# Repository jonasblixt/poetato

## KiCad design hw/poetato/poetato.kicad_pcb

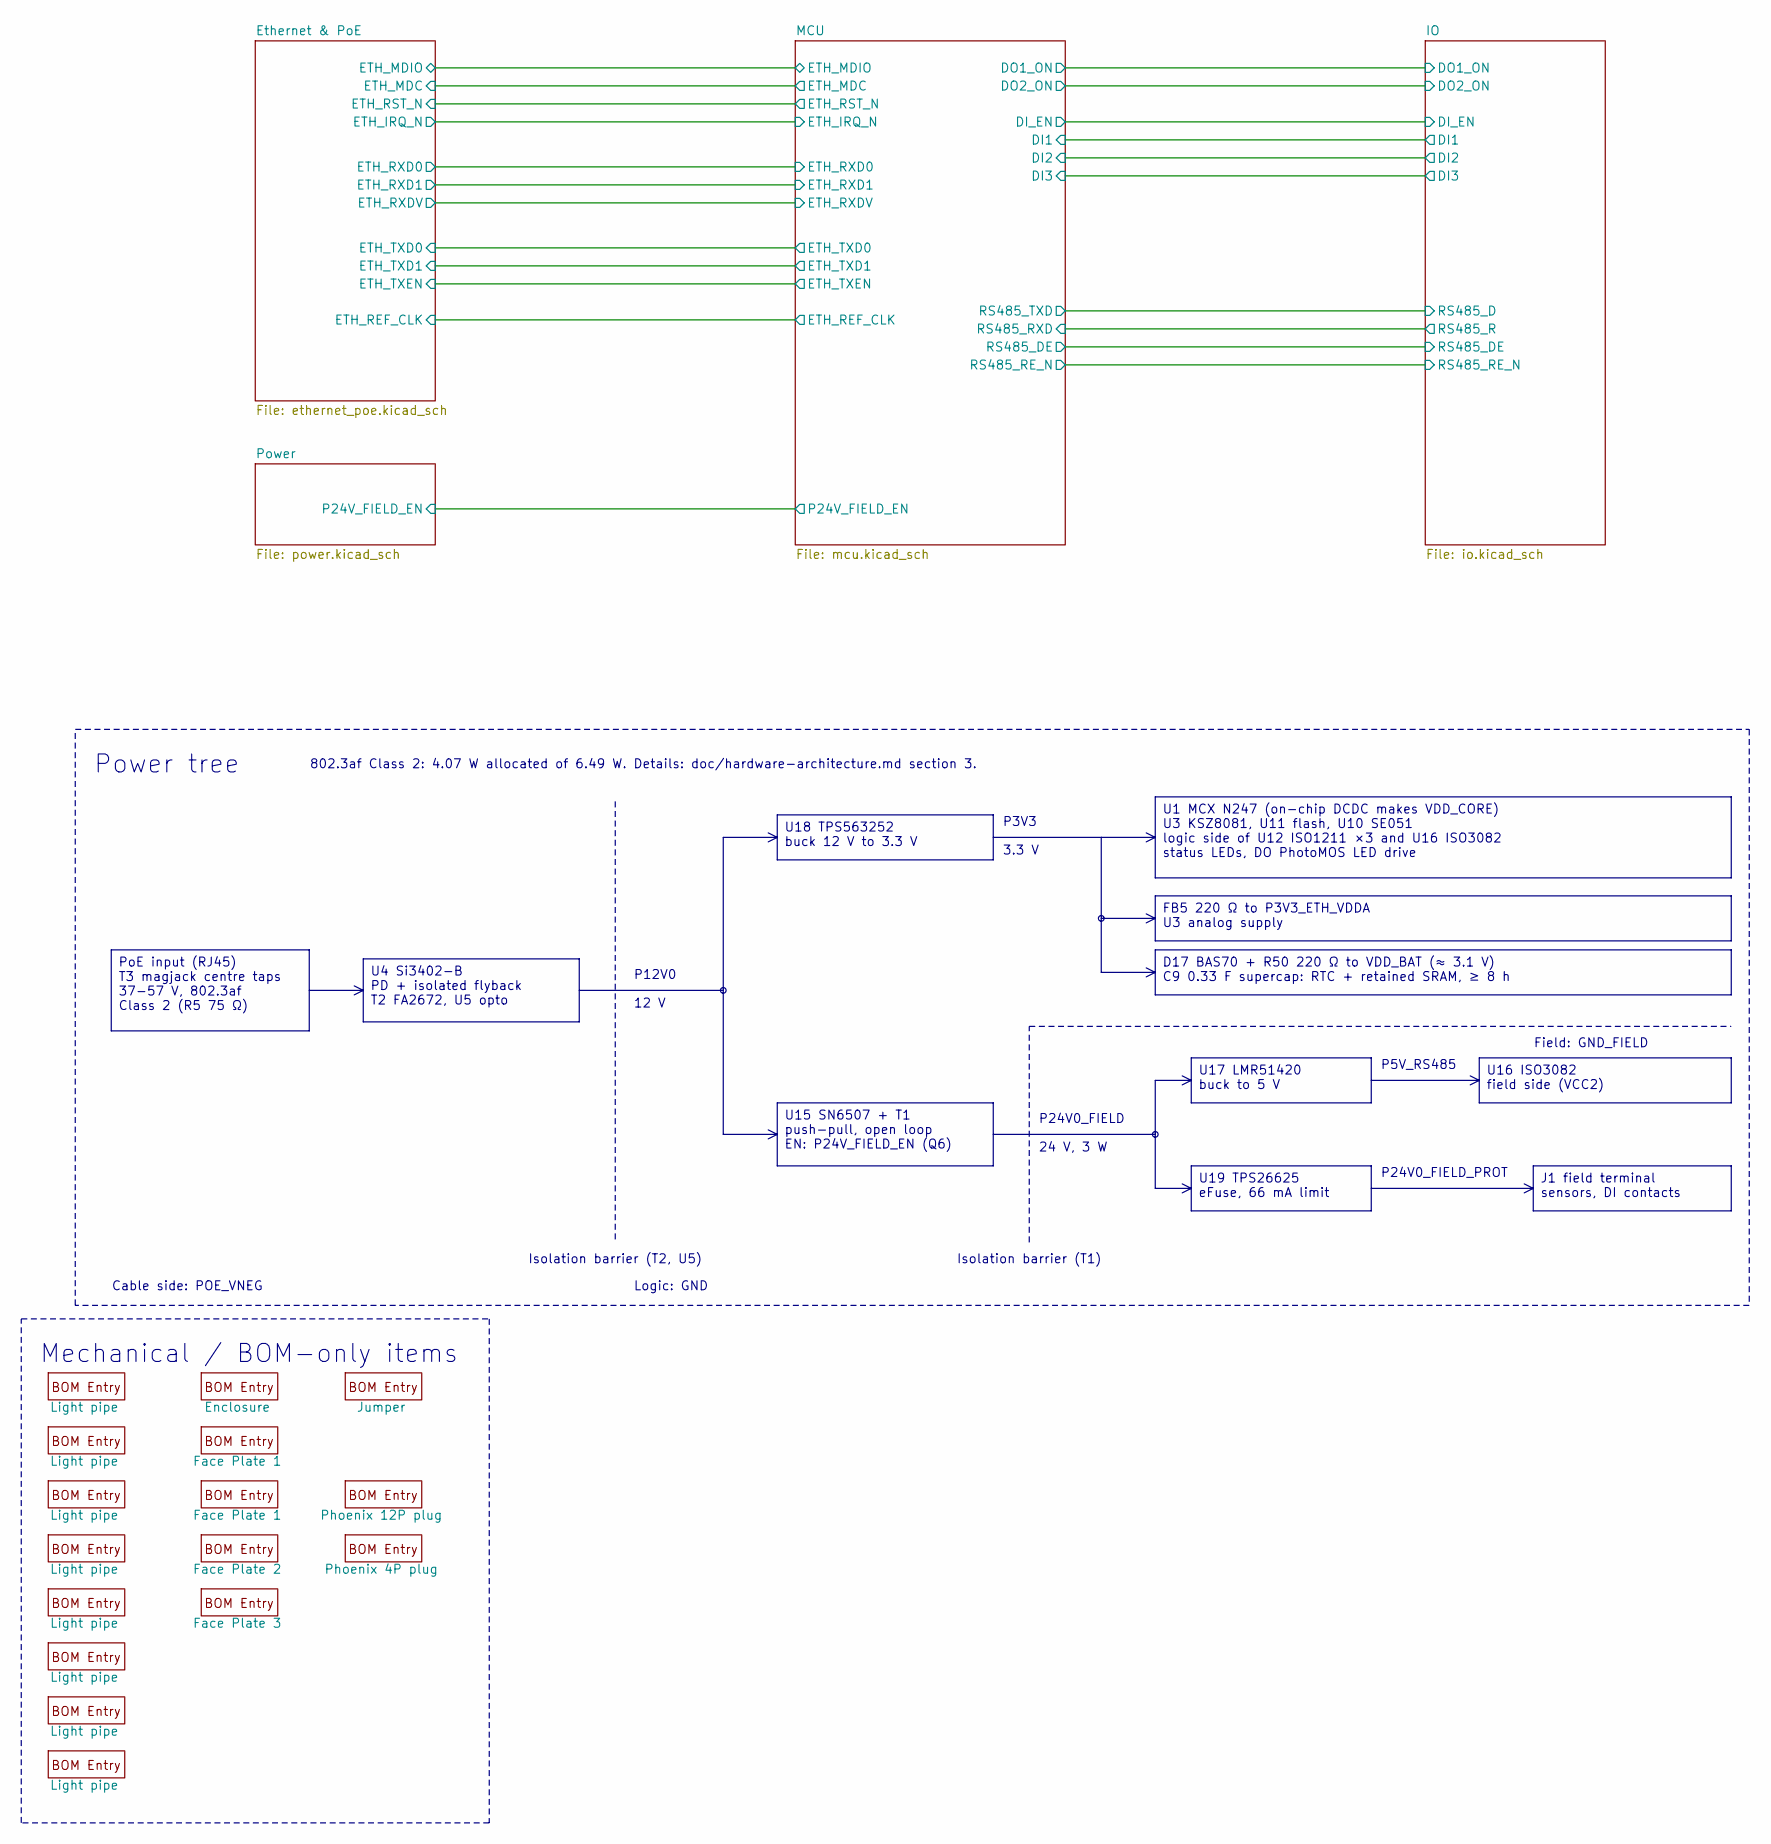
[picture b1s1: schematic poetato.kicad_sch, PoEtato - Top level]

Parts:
M1, M2, M3, M4, M5, M6, M7, M8: Light pipe; Part Number PLP2-750
M9: Enclosure; Part Number 35.0807000.BL
M10: Jumper; Part Number 60900213421
M11, M12: Face Plate 1; Part Number P05040206T.BL
M13: Face Plate 2; Part Number P05040201T.BL
M14: Face Plate 3; Part Number P05040254T.BL
M15: Phoenix 12P plug; Part Number 1757116
M16: Phoenix 4P plug; Part Number 1757035

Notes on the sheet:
P12V0
802.3af Class 2: 4.07 W allocated of 6.49 W. Details: doc/hardware-architecture.md section 3.
P5V_RS485
Power tree
P3V3
P24V0_FIELD_PROT
Field: GND_FIELD
Mechanical / BOM-only items
Logic: GND
Isolation barrier (T1)
Isolation barrier (T2, U5)
24 V, 3 W
Cable side: POE_VNEG
12 V
P24V0_FIELD
3.3 V
U18 TPS563252 buck 12 V to 3.3 V
U15 SN6507 + T1 push-pull, open loop EN: P24V_FIELD_EN (Q6)
U16 ISO3082 field side (VCC2)
PoE input (RJ45) T3 magjack centre taps 37-57 V, 802.3af Class 2 (R5 75 Ω)
FB5 220 Ω to P3V3_ETH_VDDA U3 analog supply
U19 TPS26625 eFuse, 66 mA limit
D17 BAS70 + R50 220 Ω to VDD_BAT (≈ 3.1 V) C9 0.33 F supercap: RTC + retained SRAM, ≥ 8 h
U1 MCX N247 (on-chip DCDC makes VDD_CORE) U3 KSZ8081, U11 flash, U10 SE051 logic side of U12 ISO1211 ×3 and U16 ISO3082 status LEDs, DO PhotoMOS LED drive
U4 Si3402-B PD + isolated flyback T2 FA2672, U5 opto
J1 field terminal sensors, DI contacts
U17 LMR51420 buck to 5 V

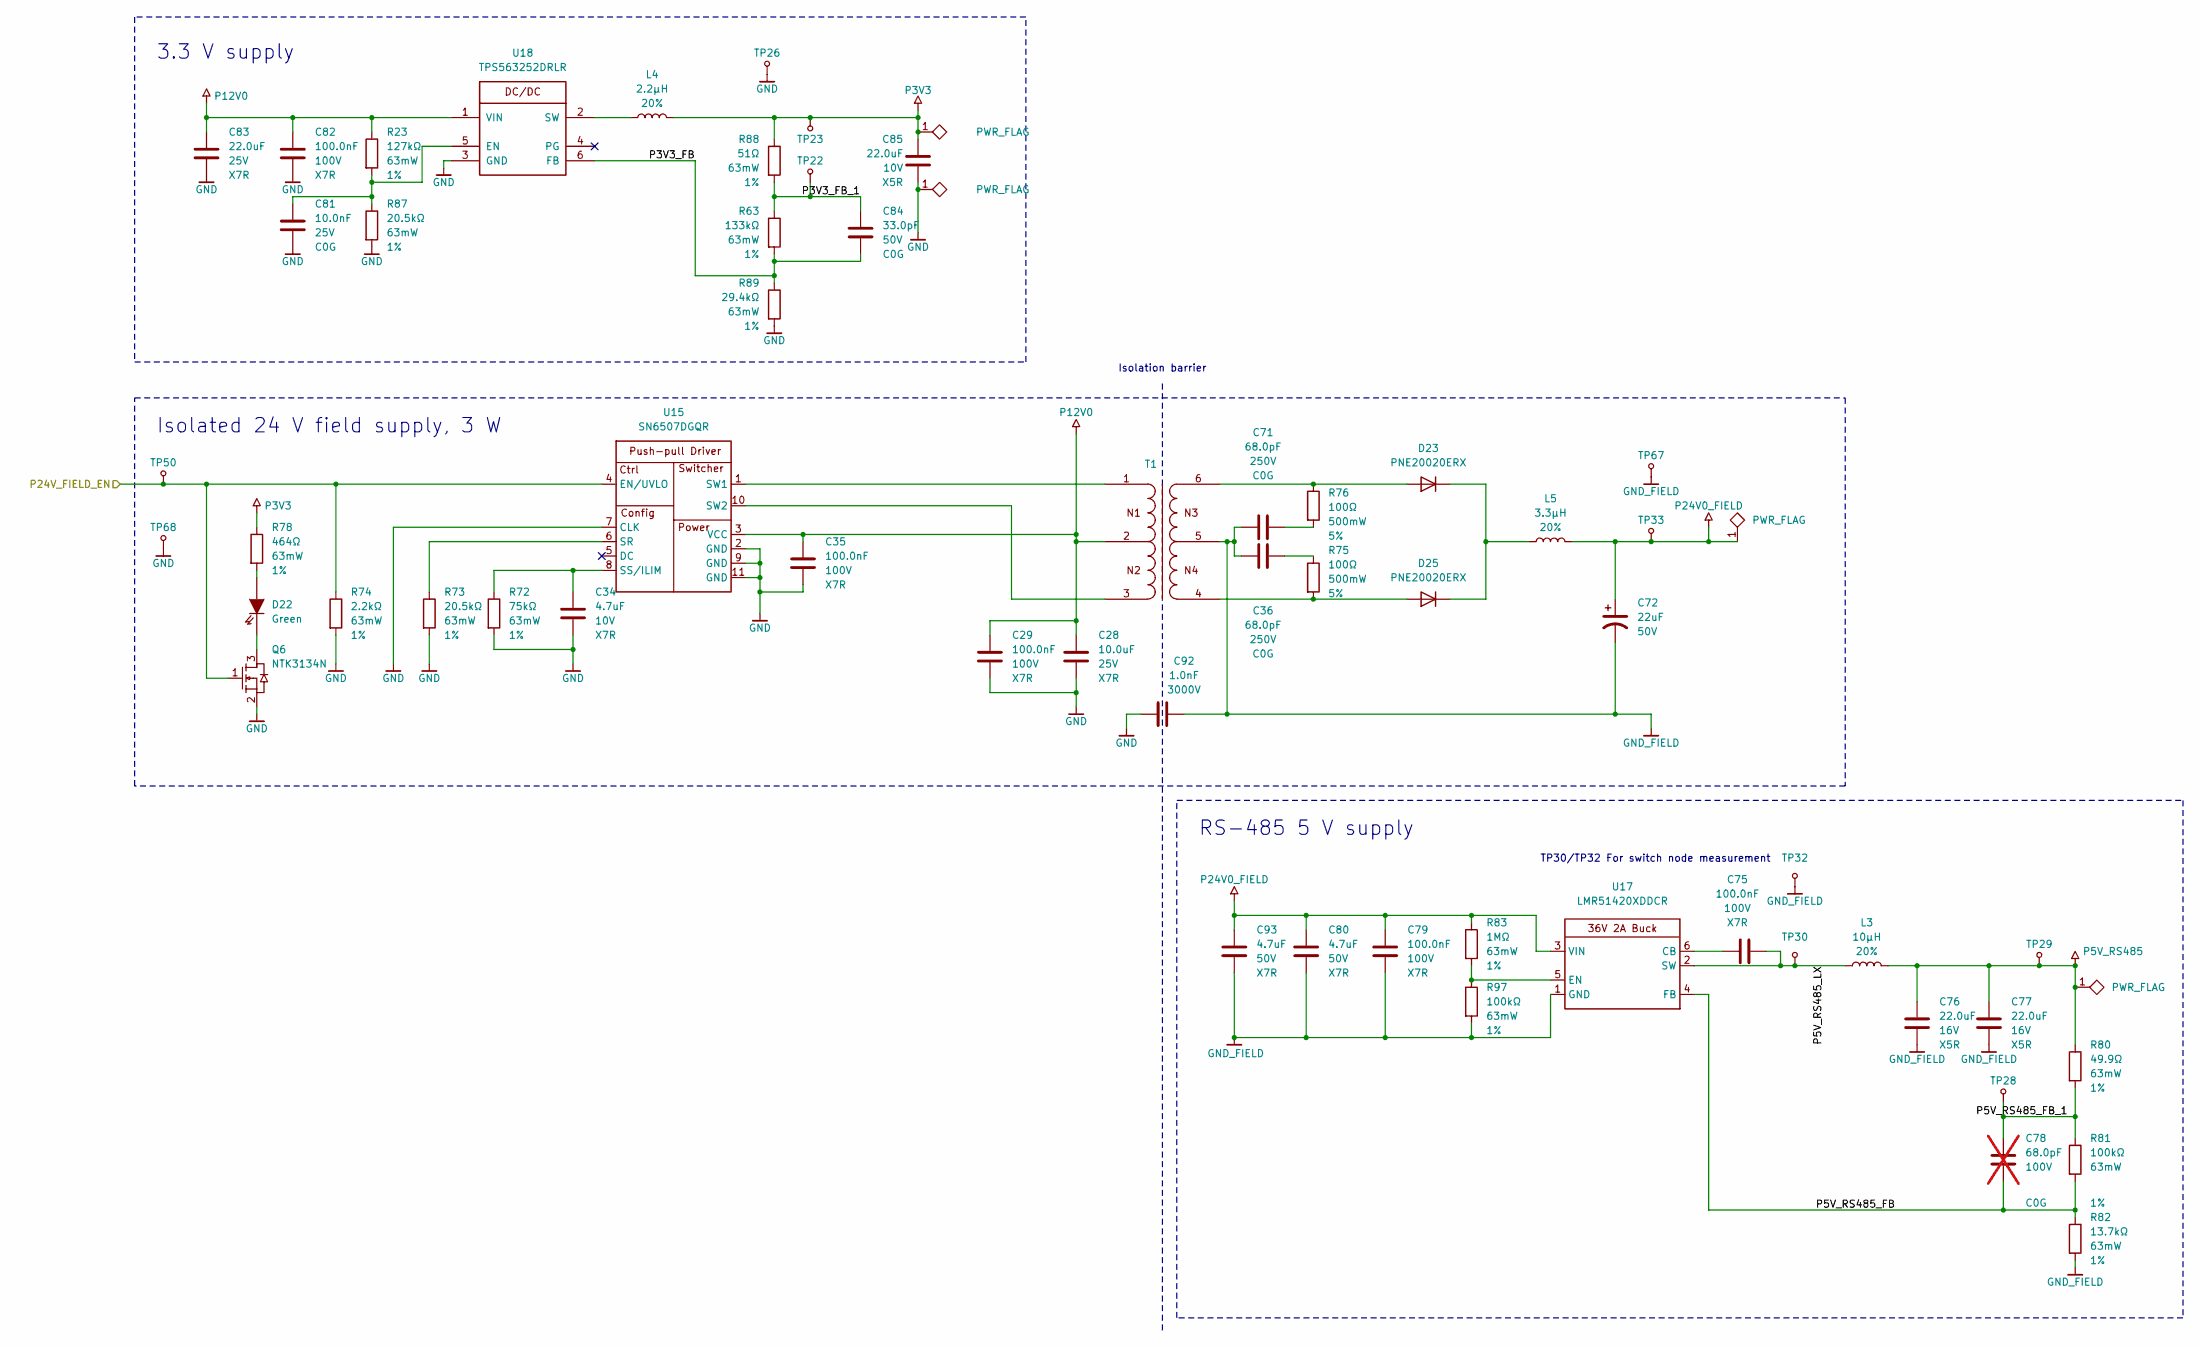
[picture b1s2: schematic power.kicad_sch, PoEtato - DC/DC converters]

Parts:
C28: 10.0uF; C_0805_2012Metric; Voltage 25V; Part Number GRM21BZ71E106KE15
C29, C35, C75, C79, C82: 100.0nF; C_0603_1608Metric; Voltage 100V; Part Number GRM188R72A104KA35
C34: 4.7uF; C_0603_1608Metric; Voltage 10V; Part Number GRM188Z71A475KE15
C36, C71: 68.0pF; C_0603_1608Metric; Voltage 250V; Part Number GQM1875C2E680JB12
C72: 22uF; CP_Elec_5x5.8; Voltage 50V; Part Number EMZR500ARA220ME61G
C76, C77: 22.0uF; C_0805_2012Metric; Voltage 16V; Part Number GRM21BR61C226ME44
C78: 68.0pF; C_0402_1005Metric; Voltage 100V; Part Number GRM1555C2A680JA01; not fitted
C80, C93: 4.7uF; C_1206_3216Metric; Voltage 50V; Part Number GRM31CR71H475KA12
C81: 10.0nF; C_0402_1005Metric; Voltage 25V; Part Number GRM1555C1E103JE01
C83: 22.0uF; C_1210_3225Metric; Voltage 25V; Part Number GRM32ER71E226KE15
C84: 33.0pF; C_0402_1005Metric; Voltage 50V; Part Number GRM1555C1H330GA01
C85: 22.0uF; C_0603_1608Metric; Voltage 10V; Part Number GRM188R61A226ME15
C92: 1.0nF; C_1808_4520Metric; Voltage 3000V; Part Number C1808C102KHRACTU
D22: LED0402_150040VS73240; LED_0402_1005Metric; Part Number 150040VS73240
D23, D25: PNE20020ERX; Nexperia_CFP3_SOD-123W; Part Number PNE20020ERX
L3: 10µH; IHLP2020CZ; Tolerance 20%; Part Number IHLP2020CZER100M01
L4: 2.2µH; IHLP1212BZ; Tolerance 20%; Part Number IHLP1212BZEZ2R2M1Z
L5: 3.3µH; IHLP1212BZ; Tolerance 20%; Part Number IHLP1212BZEZ3R3M1Z
Q6: NTK3134N; SOT-723; Part Number NTK3134NT1G
R23: 127kΩ; R_0402_1005Metric; Tolerance 1%; Part Number CRCW0402127KFKED
R63: 133kΩ; R_0402_1005Metric; Tolerance 1%; Part Number CRCW0402133KFKED
R72: 75kΩ; R_0402_1005Metric; Tolerance 1%; Part Number CRCW040275K0FKED
R73, R87: 20.5kΩ; R_0402_1005Metric; Tolerance 1%; Part Number CRCW040220K5FKED
R74: 2.2kΩ; R_0402_1005Metric; Tolerance 1%; Part Number CRCW04022K20FKED
R75, R76: 100Ω; R_1210_3225Metric; Tolerance 5%; Part Number ERJT14J101U
R78: 464Ω; R_0402_1005Metric; Tolerance 1%; Part Number CRCW0402464RFKED
R80: 49.9Ω; R_0402_1005Metric; Tolerance 1%; Part Number CRCW040249R9FKED
R81, R97: 100kΩ; R_0402_1005Metric; Tolerance 1%; Part Number CRCW0402100KFKED
R82: 13.7kΩ; R_0402_1005Metric; Tolerance 1%; Part Number CRCW040213K7FKED
R83: 1MΩ; R_0402_1005Metric; Tolerance 1%; Part Number CRCW04021M00FKED
R88: 51Ω; R_0402_1005Metric; Tolerance 1%; Part Number CRCW040251R0FKED
R89: 29.4kΩ; R_0402_1005Metric; Tolerance 1%; Part Number CRCW040229K4FKED
T1: 1308_750319693; T_Wurth_WE-PPTI-1308; Part Number 750319693
TP22, TP23, TP26, TP28, TP29, TP30, TP32, TP33, TP50, TP67, TP68: TP; TestPoint_Pad_D1.0mm
U15: SN6507DGQR; HVSSOP-10-1EP_3x3mm_P0.5mm_EP1.83x1.89mm; Part Number SN6507DGQR
U17: LMR51420XDDCR; TSOT-23-6; Part Number LMR51420XDDCR
U18: TPS563252DRLR; SOT-563; Part Number TPS563252DRLR

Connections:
/MCU/P24V_FIELD_EN: Q6.1, R74.1, TP50.1, U15.4 (EN/UVLO); also elsewhere on the board
/Power/P3V3_FB: C84.2, R63.2, R89.1, U18.6 (FB)
/Power/P3V3_FB_1: C84.1, R63.1, R88.2, TP22.1
/Power/P5V_RS485_FB: C78.2, R81.2, R82.1, U17.4 (FB)
/Power/P5V_RS485_FB_1: C78.1, R80.2, R81.1, TP28.1
/Power/P5V_RS485_LX: C75.1, L3.2, TP30.1, U17.2 (SW)
GND: C28.2, C29.2, C34.2, C35.2, C81.2, C82.2, C83.2, C85.2, C92.1, Q6.2, R72.2, R73.2, R74.2, R87.2, R89.2, TP26.1, TP68.1, U15.2 (GND), U15.7 (CLK), U15.9 (GND), U15.11 (GND), U18.3 (GND); also elsewhere on the board
GND_FIELD: C36.1, C71.1, C72.2, C76.2, C77.2, C79.1, C80.2, C92.2, C93.2, R82.2, R97.2, T1.5, TP32.1, TP67.1, U17.1 (GND); also elsewhere on the board
unnamed: C36.2, R75.1
unnamed: C71.2, R76.2
unnamed: D22.1, Q6.3
unnamed: D22.2, R78.2
unnamed: D23.2 (A), R76.1, T1.6
unnamed: D23.1 (K), D25.1 (K), L5.1
unnamed: D25.2 (A), R75.2, T1.4
unnamed: R73.1, U15.6 (SR)
unnamed: C34.1, R72.1, U15.8 (SS/ILIM)
unnamed: T1.1, U15.1 (SW1)
unnamed: T1.3, U15.10 (SW2)
unnamed: C75.2, U17.6 (CB)
unnamed: R83.2, R97.1, U17.5 (EN)
unnamed: C81.1, R23.2, R87.1, U18.5 (EN)
unnamed: L4.2, U18.2 (SW)
P3V3: C85.1, L4.1, R78.1, R88.1, TP23.1; also elsewhere on the board
P5V_RS485: C76.1, C77.1, L3.1, R80.1, TP29.1; also elsewhere on the board
P12V0: C28.1, C29.1, C35.1, C82.1, C83.1, R23.1, T1.2, U15.3 (VCC), U18.1 (VIN); also elsewhere on the board
P24V0_FIELD: C72.1, C79.2, C80.1, C93.1, L5.2, R83.1, TP33.1, U17.3 (VIN); also elsewhere on the board

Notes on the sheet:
3.3 V supply
RS-485 5 V supply
TP30/TP32 For switch node measurement
Isolated 24 V field supply, 3 W
Isolation barrier

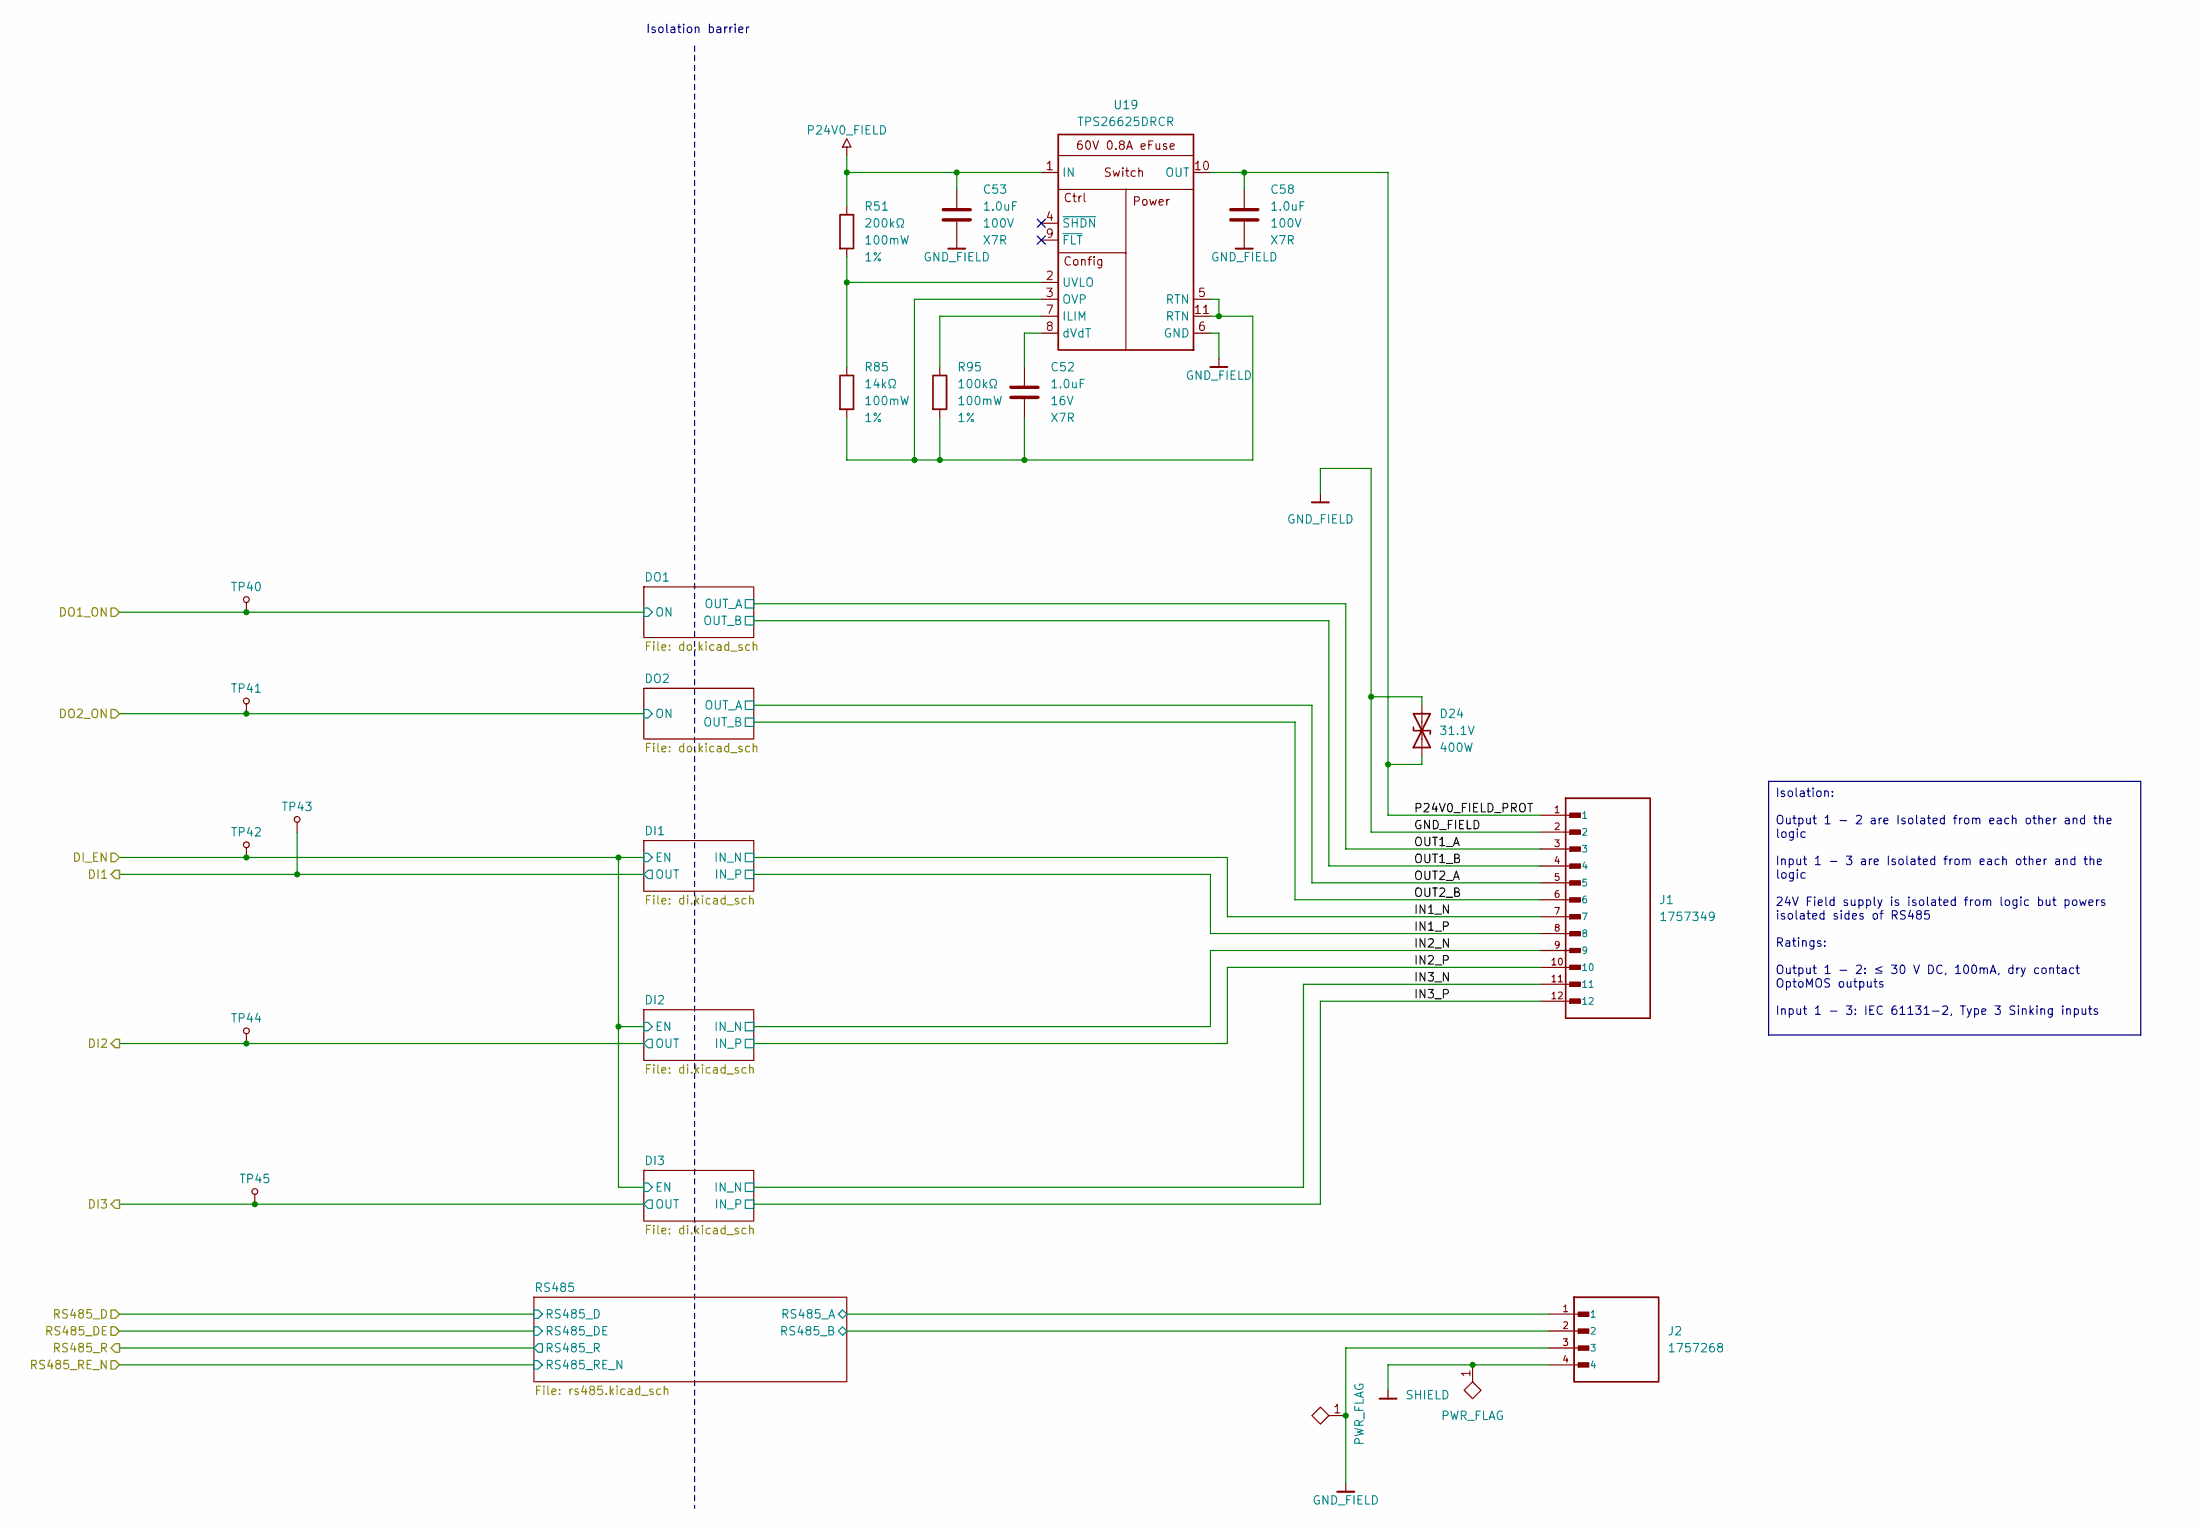
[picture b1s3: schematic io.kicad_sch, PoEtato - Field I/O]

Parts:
C52: 1.0uF; C_0805_2012Metric; Voltage 16V; Part Number GRM21BR71C105KA01
C53, C58: 1.0uF; C_1206_3216Metric; Voltage 100V; Part Number GRM31CR72A105KA01
D24: 31.1V; D_SMA; Breakdown Voltage 31.1V; Standoff Voltage 28V; Part Number SMAJ28CA
J1: 1757349; PhoenixContact_MSTBA_2,5_12-G-5,08_1x12_P5.08mm_Horizontal; Part Number 1757349
J2: 1757268; PhoenixContact_MSTBA_2,5_4-G-5,08_1x04_P5.08mm_Horizontal; Part Number 1757268
R51: 200kΩ; R_0603_1608Metric; Tolerance 1%; Part Number CRCW0603200KFKEA
R85: 14kΩ; R_0603_1608Metric; Tolerance 1%; Part Number CRCW060314K0FKEA
R95: 100kΩ; R_0603_1608Metric; Tolerance 1%; Part Number CRCW0603100KFKEA
TP40, TP41, TP42, TP43, TP44, TP45: TP; TestPoint_Pad_D1.0mm
U19: TPS26625DRCR; VSON-10-1EP_3x3mm_P0.5mm_EP1.65x2.4mm; Part Number TPS26625DRCR

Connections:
/IO/DI1: TP43.1; also elsewhere on the board
/IO/DI2: TP44.1; also elsewhere on the board
/IO/DI3: TP45.1; also elsewhere on the board
/IO/DI_EN: TP42.1; also elsewhere on the board
/IO/IN1_N: J1.7; also elsewhere on the board
/IO/IN1_P: J1.8; also elsewhere on the board
/IO/IN2_N: J1.9; also elsewhere on the board
/IO/IN2_P: J1.10; also elsewhere on the board
/IO/IN3_N: J1.11; also elsewhere on the board
/IO/IN3_P: J1.12; also elsewhere on the board
/IO/OUT1_A: J1.3; also elsewhere on the board
/IO/OUT1_B: J1.4; also elsewhere on the board
/IO/OUT2_A: J1.5; also elsewhere on the board
/IO/OUT2_B: J1.6; also elsewhere on the board
/IO/P24V0_FIELD_PROT: C58.1, D24.1 (A1), J1.1, U19.10 (OUT)
/IO/RS485/RS485_A: J2.1; also elsewhere on the board
/IO/RS485/RS485_B: J2.2; also elsewhere on the board
/MCU/DO1_ON: TP40.1; also elsewhere on the board
/MCU/DO2_ON: TP41.1; also elsewhere on the board
GND_FIELD: C53.2, C58.2, D24.2 (A2), J1.2, J2.3, U19.6 (GND); also elsewhere on the board
unnamed: R95.1, U19.7 (ILIM)
unnamed: C52.2, R85.2, R95.2, U19.3 (OVP), U19.5 (RTN), U19.11 (RTN)
unnamed: R51.2, R85.1, U19.2 (UVLO)
unnamed: C52.1, U19.8 (dVdT)
P24V0_FIELD: C53.1, R51.1, U19.1 (IN); also elsewhere on the board
SHIELD: J2.4; also elsewhere on the board

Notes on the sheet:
Isolation barrier
Isolation: Output 1 - 2 are Isolated from each other and the logic Input 1 - 3 are Isolated from each other and the logic 24V Field supply is isolated from logic but powers isolated sides of RS485 Ratings: Output 1 - 2: ≤ 30 V DC, 100mA, dry contact OptoMOS outputs Input 1 - 3: IEC 61131-2, Type 3 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

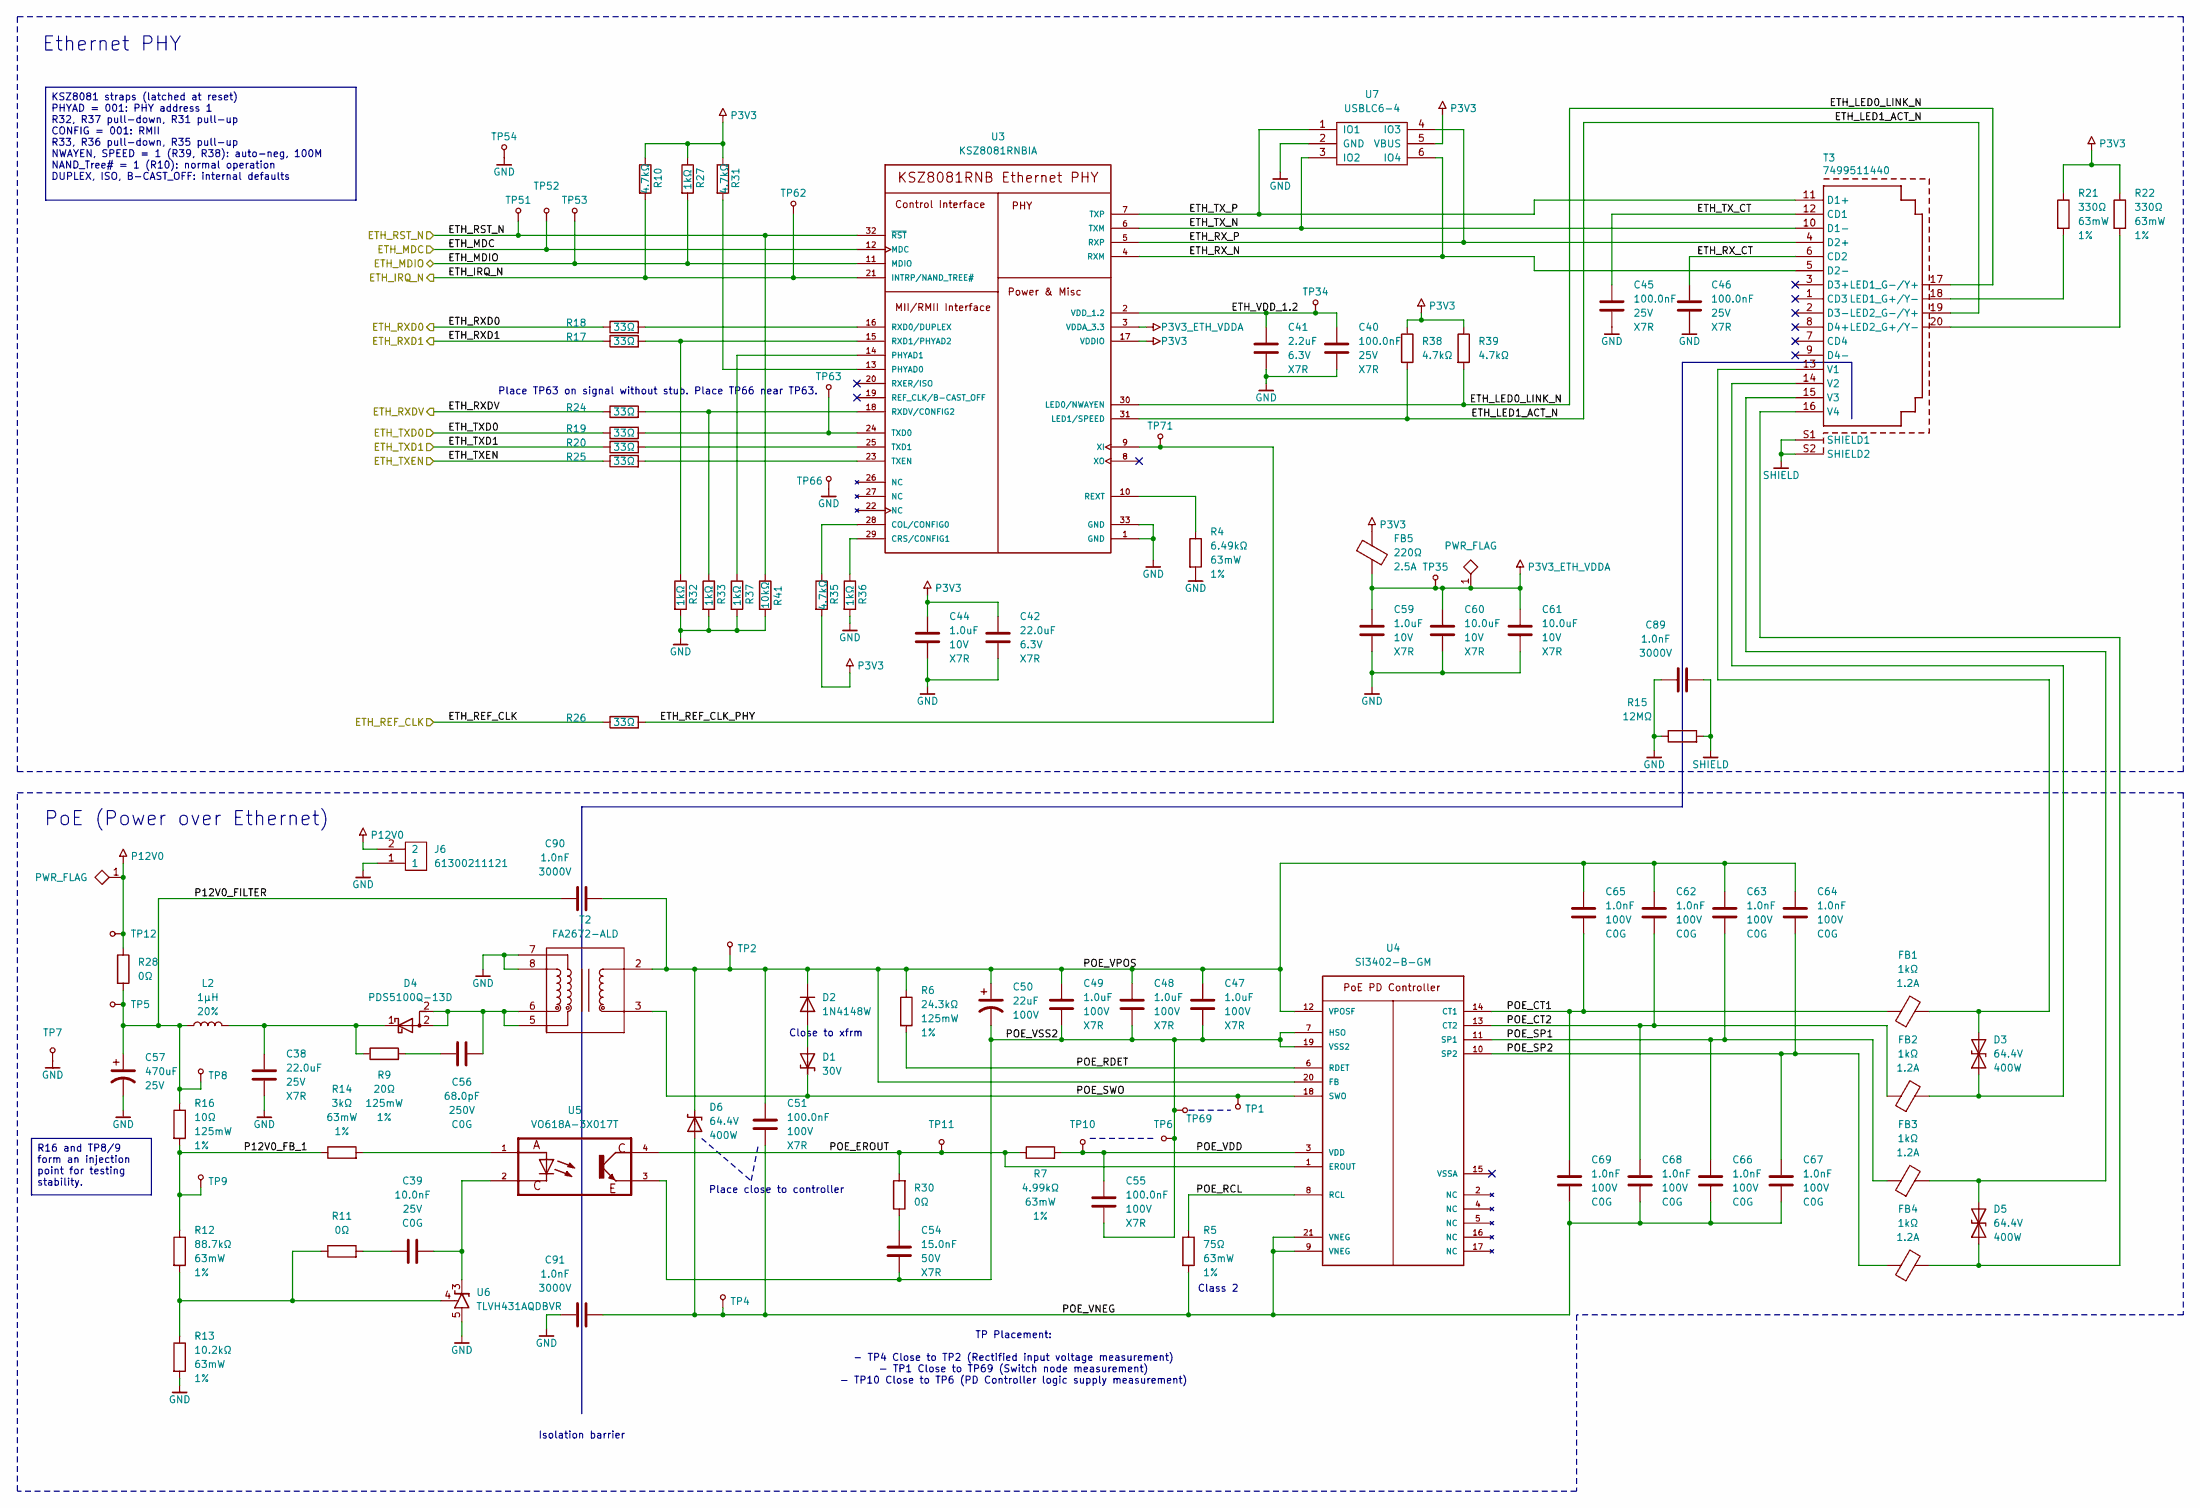
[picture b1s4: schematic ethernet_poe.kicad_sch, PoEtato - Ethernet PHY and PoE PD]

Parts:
C38: 22.0uF; C_1210_3225Metric; Voltage 25V; Part Number GRM32ER71E226KE15
C39: 10.0nF; C_0402_1005Metric; Voltage 25V; Part Number GRM1555C1E103JE01
C40, C45, C46: 100.0nF; C_0402_1005Metric; Voltage 25V; Part Number GRM155R71E104KE14
C41: 2.2uF; C_0603_1608Metric; Voltage 6.3V; Part Number GRM188R70J225KE15
C42: 22.0uF; C_0805_2012Metric; Voltage 6.3V; Part Number GRM21BZ70J226ME44
C44, C59: 1.0uF; C_0402_1005Metric; Voltage 10V; Part Number GRM155Z71A105KE01
C47, C48, C49: 1.0uF; C_1206_3216Metric; Voltage 100V; Part Number GRM31CR72A105KA01
C50: 22uF; CP_Elec_8x10; Voltage 100V; Part Number EMVE101ARA220MHA0G
C51, C55: 100.0nF; C_0603_1608Metric; Voltage 100V; Part Number GRM188R72A104KA35
C54: 15.0nF; C_0402_1005Metric; Voltage 50V; Part Number GRM155R71H153KA12
C56: 68.0pF; C_0805_2012Metric; Voltage 250V; Part Number GRM21A5C2E680FW01
C57: 470uF; CP_Elec_8x10; Voltage 25V; Part Number EMZL250ARA471MHA0G
C60, C61: 10.0uF; C_0805_2012Metric; Voltage 10V; Part Number GRM21BR71A106KA73
C62, C63, C64, C65, C66, C67, C68, C69: 1.0nF; C_0603_1608Metric; Voltage 100V; Part Number GRM1885C2A102JA01
C89, C90, C91: 1.0nF; C_1808_4520Metric; Voltage 3000V; Part Number C1808C102KHRACTU
D1: 30V; D_PowerDI-123; Part Number DFLT30A-7
D2: 1N4148W; D_SOD-123; Part Number 1N4148W
D3, D5: 64.4V; D_SMA; Breakdown Voltage 64.4V; Standoff Voltage 58V; Part Number SMAJ58CA
D4: PDS5100Q-13D; D_PowerDI-5; Part Number PDS5100Q-13D
D6: 64.4V; D_SMA; Breakdown Voltage 64.4V; Standoff Voltage 58V; Part Number SMAJ58A
FB1, FB2, FB3, FB4: 1kΩ; L_0603_1608Metric; Tolerance ±25%; Part Number BLM18SP102SH1
FB5: 220Ω; L_0603_1608Metric; Tolerance ±25%; Part Number BLM18SG221TN1
J6: 61300211121; PinHeader_1x02_P2.54mm_Vertical; Part Number 61300211121
L2: 1µH; IHLP1212AE; Tolerance 20%; Part Number IHLP1212AEEZ1R0M1Z
R4: 6.49kΩ; R_0402_1005Metric; Tolerance 1%; Part Number CRCW04026K49FKED
R5: 75Ω; R_0402_1005Metric; Tolerance 1%; Part Number CRCW040275R0FKED
R6: 24.3kΩ; R_0805_2012Metric; Tolerance 1%; Part Number CRCW080524K3FKEA
R7: 4.99kΩ; R_0402_1005Metric; Tolerance 1%; Part Number CRCW04024K99FKED
R9: 20Ω; R_0805_2012Metric; Tolerance 1%; Part Number CRCW080520R0FKEA
R10, R31, R35, R38, R39: 4.7kΩ; R_0402_1005Metric; Tolerance 1%; Part Number CRCW04024K70FKED
R11, R30: 0Ω; R_0402_1005Metric; Part Number CRCW04020000Z0EDHP
R12: 88.7kΩ; R_0402_1005Metric; Tolerance 1%; Part Number CRCW040288K7FKED
R13: 10.2kΩ; R_0402_1005Metric; Tolerance 1%; Part Number CRCW040210K2FKED
R14: 3kΩ; R_0402_1005Metric; Tolerance 1%; Part Number CRCW04023K00FKED
R15: 12MΩ; R_2512_6332Metric; Part Number CRHV2512AF12M0FKE5
R16: 10Ω; R_0805_2012Metric; Tolerance 1%; Part Number CRCW080510R0FKEA
R17, R18, R19, R20, R24, R25, R26: 33Ω; R_0402_1005Metric; Tolerance 1%; Part Number CRCW040233R0FKED
R21, R22: 330Ω; R_0402_1005Metric; Tolerance 1%; Part Number CRCW0402330RFKED
R27, R32, R33, R36, R37: 1kΩ; R_0402_1005Metric; Tolerance 1%; Part Number CRCW04021K00FKED
R28: 0Ω; R_0805_2012Metric; Part Number CRCW08050000Z0EAHP
R41: 10kΩ; R_0402_1005Metric; Tolerance 1%; Part Number CRCW040210K0FKED
T2: FA2672-ALD; Coilcraft_FA2672; Part Number FA2672-ALD
T3: 7499511440; T_Wurth_WE-RJ45LAN_7499511440; Part Number 7499511440
TP1, TP2, TP4, TP5, TP6, TP7, TP8, TP9, TP10, TP11, TP12, TP34, TP35, TP51, TP52, TP53, TP54, TP62, TP63, TP66, TP69, TP71: TP; TestPoint_Pad_D1.0mm
U3: KSZ8081RNBIA; QFN-32-1EP_5x5mm_P0.5mm_EP3.1x3.1mm; Part Number KSZ8081RNBIA
U4: Si3402-B-GM; QFN-20_5x5mm_EP2.7x2.7mm_P0.8mm; Part Number Si3402-B-GM
U5: VO618A-3X017T; Vishay_SOIC254P1016X440-4N; Part Number VO618A-3X017T
U6: TLVH431AQDBVR; SOT-23-5; Part Number TLVH431AQDBVR
U7: USBLC6-4; SOT-23-6; Part Number USBLC6-4SC6Y

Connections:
/Ethernet & PoE/ETH_IRQ_N: R10.2, TP62.1, U3.21 (INTRP/NAND_TREE#); also elsewhere on the board
/Ethernet & PoE/ETH_LED0_LINK_N: R39.2, T3.17 (LED1_G-/Y+), U3.30 (LED0/NWAYEN)
/Ethernet & PoE/ETH_LED1_ACT_N: R38.2, T3.19 (LED2_G-/Y+), U3.31 (LED1/SPEED)
/Ethernet & PoE/ETH_MDC: TP52.1, U3.12 (MDC); also elsewhere on the board
/Ethernet & PoE/ETH_MDIO: R27.2, TP53.1, U3.11 (MDIO); also elsewhere on the board
/Ethernet & PoE/ETH_REF_CLK: R26.1; also elsewhere on the board
/Ethernet & PoE/ETH_REF_CLK_PHY: R26.2, TP71.1, U3.9 (XI)
/Ethernet & PoE/ETH_RST_N: R41.1, TP51.1, U3.32 (~RST); also elsewhere on the board
/Ethernet & PoE/ETH_RXD0: R18.1; also elsewhere on the board
/Ethernet & PoE/ETH_RXD1: R17.1; also elsewhere on the board
/Ethernet & PoE/ETH_RXDV: R24.1; also elsewhere on the board
/Ethernet & PoE/ETH_RX_CT: C46.1, T3.6 (CD2)
/Ethernet & PoE/ETH_RX_N: T3.5 (D2-), U3.4 (RXM), U7.6 (IO4)
/Ethernet & PoE/ETH_RX_P: T3.4 (D2+), U3.5 (RXP), U7.4 (IO3)
/Ethernet & PoE/ETH_TXD0: R19.1; also elsewhere on the board
/Ethernet & PoE/ETH_TXD1: R20.1; also elsewhere on the board
/Ethernet & PoE/ETH_TXEN: R25.1; also elsewhere on the board
/Ethernet & PoE/ETH_TX_CT: C45.1, T3.12 (CD1)
/Ethernet & PoE/ETH_TX_N: T3.10 (D1-), U3.6 (TXM), U7.3 (IO2)
/Ethernet & PoE/ETH_TX_P: T3.11 (D1+), U3.7 (TXP), U7.1 (IO1)
/Ethernet & PoE/ETH_VDD_1.2: C40.1, C41.1, TP34.1, U3.2 (VDD_1.2)
/Ethernet & PoE/P12V0_FB_1: R12.1, R14.1, R16.2, TP9.1
/Ethernet & PoE/P12V0_FILTER: C57.1, C90.1, L2.1, R16.1, R28.2, TP5.1, TP8.1
/Ethernet & PoE/POE_CT1: C65.2, C69.1, FB1.1, U4.14 (CT1)
/Ethernet & PoE/POE_CT2: C62.2, C68.1, FB2.1, U4.13 (CT2)
/Ethernet & PoE/POE_EROUT: R7.1, R30.2, TP11.1, U4.1 (EROUT), U5.4
/Ethernet & PoE/POE_RCL: R5.1, U4.8 (RCL)
/Ethernet & PoE/POE_RDET: R6.2, U4.6 (RDET)
/Ethernet & PoE/POE_SP1: C63.2, C66.1, FB3.1, U4.11 (SP1)
/Ethernet & PoE/POE_SP2: C64.2, C67.1, FB4.1, U4.10 (SP2)
/Ethernet & PoE/POE_SWO: D1.1 (A1), T2.3, TP1.1, U4.18 (SWO)
/Ethernet & PoE/POE_VDD: C55.1, R7.2, TP10.1, U4.3 (VDD)
/Ethernet & PoE/POE_VNEG: C51.2, C66.2, C67.2, C68.2, C69.2, C91.2, D6.2 (A2), R5.2, TP4.1, U4.9 (VNEG), U4.21 (VNEG)
/Ethernet & PoE/POE_VPOS: C47.1, C48.1, C49.1, C50.1, C51.1, C62.1, C63.1, C64.1, C65.1, C90.2, D2.1 (K), D6.1 (A1), R6.1, T2.2, TP2.1, U4.12 (VPOSF), U4.20 (FB)
/Ethernet & PoE/POE_VSS2: C47.2, C48.2, C49.2, C50.2, C54.2, C55.2, TP6.1, TP69.1, U4.7 (HSO), U4.19 (VSS2), U5.3
GND: C38.2, C40.2, C41.2, C42.2, C44.2, C45.2, C46.2, C57.2, C59.2, C60.2, C61.2, C89.1, C91.1, J6.1, R4.2, R13.2, R15.1, R32.2, R33.2, R36.2, R37.2, R41.2, T2.7, T2.8, TP7.1, TP54.1, TP66.1, U3.1 (GND), U3.33 (GND), U6.5, U7.2 (GND); also elsewhere on the board
unnamed: C39.1, R11.2
unnamed: C39.2, U5.2, U6.3
unnamed: C54.1, R30.1
unnamed: C56.1, R9.2
unnamed: D1.2 (A2), D2.2 (A)
unnamed: D3.1 (A1), FB2.2, T3.14 (V2)
unnamed: D3.2 (A2), FB1.2, T3.13 (V1)
unnamed: C56.2, D4.2 (A), T2.5, T2.6
unnamed: C38.1, D4.1 (K), L2.2, R9.1
unnamed: D5.1 (A1), FB4.2, T3.16 (V4)
unnamed: D5.2 (A2), FB3.2, T3.15 (V3)
unnamed: R11.1, R12.2, R13.1, U6.4
unnamed: R14.2, U5.1
unnamed: R21.2, T3.18 (LED1_G+/Y-)
unnamed: R22.2, T3.20 (LED2_G+/Y-)
unnamed: R35.1, U3.28 (COL/CONFIG0)
unnamed: R36.1, U3.29 (CRS/CONFIG1)
unnamed: R31.2, U3.13 (PHYAD0)
unnamed: R37.1, U3.14 (PHYAD1)
unnamed: R4.1, U3.10 (REXT)
unnamed: R18.2, U3.16 (RXD0/DUPLEX)
unnamed: R17.2, R32.1, U3.15 (RXD1/PHYAD2)
unnamed: R24.2, R33.1, U3.18 (RXDV/CONFIG2)
unnamed: R19.2, TP63.1, U3.24 (TXD0)
unnamed: R20.2, U3.25 (TXD1)
unnamed: R25.2, U3.23 (TXEN)
P3V3: C42.1, C44.1, FB5.1, R10.1, R21.1, R22.1, R27.1, R31.1, R35.2, R38.1, R39.1, U3.17 (VDDIO), U7.5 (VBUS); also elsewhere on the board
P3V3_ETH_VDDA: C59.1, C60.1, C61.1, FB5.2, TP35.1, U3.3 (VDDA_3.3)
P12V0: J6.2, R28.1, TP12.1; also elsewhere on the board
SHIELD: C89.2, R15.2, T3.S1 (SHIELD1), T3.S2 (SHIELD2); also elsewhere on the board

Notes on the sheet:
Isolation barrier
PoE (Power over Ethernet)
Place close to controller
Ethernet PHY
Class 2
TP Placement: - TP4 Close to TP2 (Rectified input voltage measurement) - TP1 Close to TP69 (Switch node measurement) - TP10 Close to TP6 (PD Controller logic supply measurement)
Close to xfrm
Place TP63 on signal without stub. Place TP66 near TP63.
KSZ8081 straps (latched at reset) PHYAD = 001: PHY address 1 R32, R37 pull-down, R31 pull-up CONFIG = 001: RMII R33, R36 pull-down, R35 pull-up NWAYEN, SPEED = 1 (R39, R38): auto-neg, 100M NAND_Tree# = 1 (R10): normal operation DUPLEX, ISO, B-CAST_OFF: internal defaults
R16 and TP8/9 form an injection point for testing stability.

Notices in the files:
hw/poetato/di.kicad_sch:
Copyright (c) 2026 Jonas Blixt. SPDX-License-Identifier: CERN-OHL-S-2.0
Licensed under CERN-OHL-S v2: https://ohwr.org/cern_ohl_s_v2.txt
